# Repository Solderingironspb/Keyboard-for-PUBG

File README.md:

# Keyboard-for-PUBG (4 кнопочный контроллер для игры PUBG)
*Проект 4 кнопочного контроллера на RISC-V микроконтроллере CH32V203F6P6 для игры PUBG. При желании можно адаптировать под что угодно...*

*В основном мне нужны только 2 доп. педали, чтоб удобно было играть - это быстрый присед и рация. Вот ногами и делаю жмяк-жмяк :D*

*Каким бы бесполезным не казался проект, мол игрульки, детские забавы - а Вы попробуйте поднять USB на данных микроконтроллерах, напишите код. Создайте печатную плату под это все. Разработайте 3D модели устройства и педалей. Это же куча времени и полезного опыта :)*

## Особенности проекта:
* Печатная плата разработана в KiCad 8
* Есть файлы *.stl для слайсера. Все напечатано на 3D принтере.
* В папке firmware  хранятся готовые файлы прошивки CH32V203F6P6 в форматах *.hex и *.bin
* Проект написан в VSCode. Используется toolchain от MRStudio RISC-V_Embedded_GCC12. Makefile присутствует.
* Кнопка для рации: https://www.chipdip.ru/product/pbs-24b-4
* Концевой выключатель для педальки: https://www.chipdip.ru/product/msw-01
* Пружина в педальку: Толщина проволоки 1 мм, диаметр пружины 15 мм, высота пружины 32 мм.
* Винты в педальке: М5 30мм.
* Войлок в педальку для мягкого клика: 4.5 мм (из валенка) :D
* Клей, которым приклеивал войлок и резиновую подошву на педали: 88 Luxe. Рекомендую. Очень хороший клей.

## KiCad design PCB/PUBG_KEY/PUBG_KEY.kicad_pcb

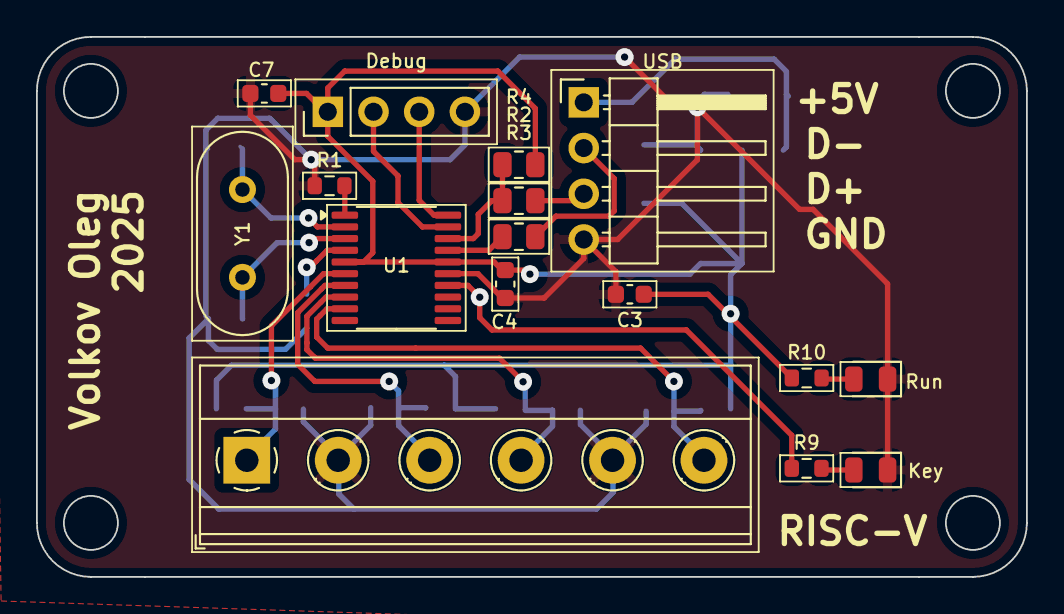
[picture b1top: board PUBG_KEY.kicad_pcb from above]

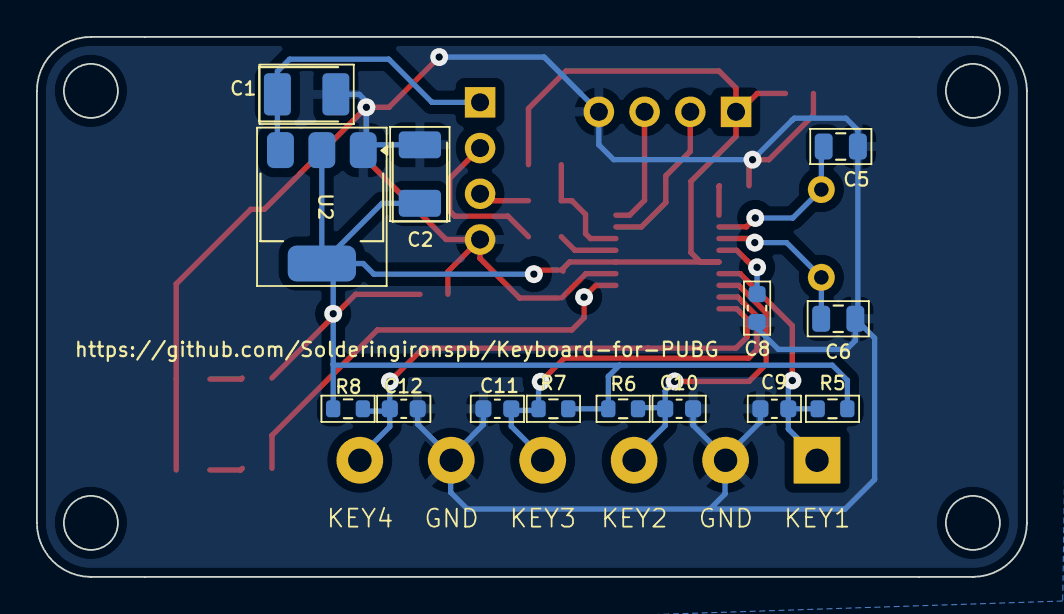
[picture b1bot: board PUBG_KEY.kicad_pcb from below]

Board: 2 copper layers, 55.0 x 30.0 mm, 30 parts (14 on the bottom side), 20 nets.

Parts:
C1, C2: 47uF; CP_EIA-3528-21_Kemet-B_Pad1.50x2.35mm_HandSolder
C3, C4, C7, C8, C9, C10, C11, C12: 100n; C_0603_1608Metric
C5, C6: 30pF; C_0805_2012Metric
Debug: Debug; PinHeader_1x04_P2.54mm_Vertical
J3: KEY_IN; TerminalBlock_Phoenix_MKDS-1,5-6-5.08_1x06_P5.08mm_Horizont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
Key: Key; D_0805_2012Metric
R1, R5, R6, R7, R8, R9, R10: 10k; R_0603_1608Metric
R2, R3: 20; R_0805_2012Metric
R4: 1.5k; R_0805_2012Metric
Run: Key; D_0805_2012Metric
U1: CH32V203F6P6; TSSOP-20_4.4x6.5mm_P0.65mm
U2: AMS1117-3.3; SOT-223-3_TabPin2
USB: USB; PinHeader_1x04_P2.54mm_Horizontal
Y1: 8MHz; Crystal_HC49-U_Vertical

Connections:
+5V: C1.1, U2.3 (VI), USB.1 (VBUS)
DM: R3.1, U1.17 (PA11/USB1DM)
DP: R2.1, R4.1, U1.18 (PA12/USB1DP)
GND: C1.2, C2.2, C3.2, C4.2, C5.1, C6.1, C7.2, C8.2, C9.2, C10.2, C11.2, C12.2, Debug.4, J3.2, J3.5, Key.1 (K), R1.1, Run.1 (K), U1.15 (VSS), U2.1 (GND), USB.4 (ID)
KEY1: C9.1, J3.1, R5.1, U1.6 (PA0/WKUP/ADC0)
KEY2: C10.1, J3.3, R6.1, U1.7 (PA1/ADC1)
KEY3: C11.1, J3.4, R7.1, U1.8 (PA2/ADC2)
KEY4: C12.1, J3.6, R8.1, U1.9 (PA3/ADC3)
LED: R9.1, U1.14 (PB1/ADC9)
unnamed: Key.2 (A), R9.2
unnamed: R10.2, Run.2 (A)
unnamed: R2.2, USB.3 (D+)
unnamed: R3.2, USB.2 (D-)
unnamed: R1.2, U1.1 (BOOT0/PB8)
unnamed: C8.1, U1.4 (NRST)
PD0: C5.2, U1.2 (OSC_IN/PD0), Y1.1
PD1: C6.2, U1.3 (OSC_OUT/PD1), Y1.2
SWCLK: Debug.3, U1.20 (PA14/SWCLK)
SWDIO: Debug.2, U1.19 (PA13/SWDIO)
VDD: C2.1, C3.1, C4.1, C7.1, Debug.1, R4.2, R5.2, R6.2, R7.2, R8.2, R10.1, U1.5 (VDDA), U1.16 (VDD), U2.2 (VO)

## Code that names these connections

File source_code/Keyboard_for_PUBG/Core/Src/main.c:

/*
 * Пример Custom HID (Keyboard) на CH32V203F6P6
 * В файле usb_desc.h можно найти основные определения:
 * - USBD_VID - VID устройства
 * - USBD_PID - PID устройства
 * - USBD_LANGID_STRING - языковой идентификатор
 * - USBD_SIZE_REPORT_DESC - размер репорт десктриптора (данный дестриптор
 * описывает геймпад)
 * - CUSTOM_HID_BINTERVAL - интервал, с которым геймпад будет опрашиваться (в
 * мс) В файле usb_desc.c можно найти основные настройки устройства:
 * - const uint8_t USBD_DeviceDescriptor[USBD_SIZE_DEVICE_DESC] - USB Device
 * Descriptors
 * - const uint8_t USBD_ConfigDescriptor[USBD_SIZE_CONFIG_DESC] - USB
 * Configration Descriptors
 * - const uint8_t USBD_HidRepDesc[USBD_SIZE_REPORT_DESC] - HID Report
 * Descriptor(он описывает наш геймпад: сколько кнопок, осей, и т.д.)
 * - uint8_t StringVendor[64] - Кастомный iManufacturer
 * - uint8_t StringProduct[64] - Кастомный iProduct
 * - const uint8_t USBD_StringSerial[USBD_SIZE_STRING_SERIAL] - Серийный номер
 * устройства (см. стр. 53 Keyboard/Keypad
 * table)https://www.usb.org/sites/default/files/documents/hut1_12v2.pdf
 *
 */
#include "main.h"
#include "hw_config.h"
#include "stdio.h"
#include "usb_desc.h"
#include "usb_lib.h"
#include "usb_prop.h"
#include "usb_pwr.h"
#include "usbd_compatibility_hid.h"

#define LED_ON  GPIOB->BSHR = GPIO_BSHR_BS1
#define LED_OFF GPIOB->BSHR = GPIO_BSHR_BR1
bool flag_led = false;
uint8_t Reset_cnt = 4;

extern uint8_t USBD_ENDPx_DataUp(uint8_t endp, uint8_t *pbuf, uint16_t len);

/*Структура нашего геймпада. В точности повторяет HID Report Descriptor*/
typedef struct __attribute__((packed)) {
    uint8_t Modifier_keys;
    uint8_t Reserved;
    uint8_t Keycode_1;
    uint8_t Keycode_2;
    uint8_t Keycode_3;
    uint8_t Keycode_4;
    uint8_t Keycode_5;
    uint8_t Keycode_6;

} USB_Custom_HID_Keyboard;

USB_Custom_HID_Keyboard Keyboard_data;

int main(void) {
    RVMSIS_Debug_init();              // Настройка дебага
    RVMSIS_RCC_SystemClock_144MHz();  // Настройка системной частоты
    RVMSIS_SysTick_Timer_init();      // Настройка системного таймера

    // Настройка GPIO
    RVMSIS_GPIO_init(GPIOB, 1, GPIO_GENERAL_PURPOSE_OUTPUT, GPIO_OUTPUT_PUSH_PULL, GPIO_SPEED_50_MHZ);  // LED
    RVMSIS_GPIO_init(GPIOA, 0, GPIO_INPUT, GPIO_INPUT_FLOATING, GPIO_SPEED_RESERVED);                   // KEY1
    RVMSIS_GPIO_init(GPIOA, 1, GPIO_INPUT, GPIO_INPUT_FLOATING, GPIO_SPEED_RESERVED);                   // KEY2
    RVMSIS_GPIO_init(GPIOA, 2, GPIO_INPUT, GPIO_INPUT_FLOATING, GPIO_SPEED_RESERVED);                   // KEY3
    RVMSIS_GPIO_init(GPIOA, 3, GPIO_INPUT, GPIO_INPUT_FLOATING, GPIO_SPEED_RESERVED);                   // KEY4

    Set_USBConfig();
    USB_Init();
    USB_Interrupts_Config();

    /*Инициализация структуры клавиатуры*/
    Keyboard_data.Modifier_keys = 0;
    Keyboard_data.Reserved = 0;
    Keyboard_data.Keycode_1 = 0x0;
    Keyboard_data.Keycode_2 = 0x0;
    Keyboard_data.Keycode_3 = 0x0;
    Keyboard_data.Keycode_4 = 0x0;
    Keyboard_data.Keycode_5 = 0x0;
    Keyboard_data.Keycode_6 = 0x0;

    while (1) {
        if (bDeviceState == CONFIGURED) {
            /*Keycode_1*/
            if (!READ_BIT(GPIOA->INDR, GPIO_INDR_IDR3)) {
                Keyboard_data.Modifier_keys = 0;
                Keyboard_data.Keycode_1 = 0x6;  // C
            } else {
                Keyboard_data.Modifier_keys = 0;
                Keyboard_data.Keycode_1 = 0;
            }

            /*Keycode_2*/
            if (!READ_BIT(GPIOA->INDR, GPIO_INDR_IDR2)) {
                Keyboard_data.Modifier_keys = 0;
                Keyboard_data.Keycode_2 = 0x17;  // T
            } else {
                Keyboard_data.Modifier_keys = 0;
                Keyboard_data.Keycode_2 = 0;
            }

            /*Keycode_3*/
            if (!READ_BIT(GPIOA->INDR, GPIO_INDR_IDR1)) {
                Keyboard_data.Modifier_keys = 0;
                Keyboard_data.Keycode_3 = 0x0C;  // I
            } else {
                Keyboard_data.Modifier_keys = 0;
                Keyboard_data.Keycode_3 = 0;
            }

            /*Keycode_4*/
            if (!READ_BIT(GPIOA->INDR, GPIO_INDR_IDR0)) {
                Keyboard_data.Modifier_keys = 0;
                Keyboard_data.Keycode_4 = 0x13;  // P
            } else {
                Keyboard_data.Modifier_keys = 0;
                Keyboard_data.Keycode_4 = 0;
            }

            /*Моргнем при активности*/
            uint8_t State = (uint8_t)(GPIOA->INDR);
            if (State < 0xF) {
                LED_ON;
            } else {
                Keyboard_data.Modifier_keys = 0;
                Keyboard_data.Reserved = 0;
                Keyboard_data.Keycode_1 = 0x0;
                Keyboard_data.Keycode_2 = 0x0;
                Keyboard_data.Keycode_3 = 0x0;
                Keyboard_data.Keycode_4 = 0x0;
                Keyboard_data.Keycode_5 = 0x0;
                Keyboard_data.Keycode_6 = 0x0;
                LED_OFF;
            }
            // Отправим в репорт сформированный буфер
            USBD_ENDPx_DataUp(ENDP2, (uint8_t *)&Keyboard_data, sizeof(Keyboard_data));
        } else {
            LED_ON;
            Delay_ms(500);
            LED_OFF;
            Delay_ms(500);

            if (Reset_cnt) {
                Reset_cnt--;
            } else {
                NVIC_SystemReset(); //Если ПК уже 5 секунд не видит устройство - перезагрузим МК(Костыль, т.к. после перезагрузки ПК - устройство видится в диспетчере устройств, но ничего не отправляет. Каждый раз передергивать USB надоело. А как исправить этот косяк - я так и не разобрался...)
            }
        }
    }
}

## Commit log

2025-04-17 add files
2025-04-17 Update Makefile
